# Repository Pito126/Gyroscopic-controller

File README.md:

# Gyroscopic Controller

Gyroskopický ovladač postavený na mikrokontroléru **ESP32**. Tento projekt umožňuje snadné ovládání zařízení (např. her, robotů nebo dronů) pomocí pohybu ruky nebo zařízení díky vestavěnému gyroskopu a akcelerometru.

## Funkce
- **Detekce pohybu**: Real-time čtení dat z gyroskopu pro detekci rotace a akcelerace.
- **Bezdrátové připojení**: Podpora Wi-Fi a Bluetooth přes ESP32 pro snadnou integraci s aplikacemi.
- **Snadná konfigurace**: Použití Arduino IDE nebo PlatformIO pro rychlý vývoj.
- **Open-source hardware**: Kompatibilní s běžnými senzory jako MPU6050 nebo LSM6DS3 (upravte podle vašeho setupu).

## Diagramy a schémata

### Schéma zapojení (PNG)
Zde je schéma zapojení ESP32 s gyroskopickým senzorem MPU6050:

### Schéma PCB zapojení (PNG)
Zde je schéma PCB zapojení ESP32 s gyroskopickým senzorem MPU6050:

## Požadavky
- **Hardware**:
  - ESP32 development board (např. ESP32-WROOM-32).
  - Gyroskopický senzor (např. MPU6050 připojený přes I2C).
  - Jumper wires a breadboard pro prototypování.
- **Software**:
  - Arduino IDE (verze 2.0+) s ESP32 board support.
  - Knihovny: `Wire` (pro I2C), `MPU6050` (pokud používáte tento senzor) – instalujte přes Library Manager.

## Instalace
1. Nainstalujte Arduino IDE z [oficiálního webu](https://www.arduino.cc/en/software).
2. Přidejte podporu pro ESP32: V IDE jděte do **File > Preferences**, přidejte URL `https://raw.githubusercontent.com/espressif/arduino-esp32/gh-pages/package_esp32_index.json` do Additional Board Manager URLs a nainstalujte "esp32" z Board Manager.
3. Stáhněte si tento repozitář: `git clone https://github.com/Pito126/Gyroscopic-controller.git`.
4. Otevřete soubory `.ino` v Arduino IDE.
5. Nahrajte kód na ESP32 přes USB.

## Použití
1. Připojte gyroskopický senzor k ESP32 (příklad pro MPU6050):
   - VCC → 3.3V
   - GND → GND
   - SCL → GPIO 22
   - SDA → GPIO 21
2. Nahrajte sketch (příklad v `src/main.ino` – upravte podle vašeho kódu).
3. Otevřete Serial Monitor (115200 baud) pro sledování dat pohybu.

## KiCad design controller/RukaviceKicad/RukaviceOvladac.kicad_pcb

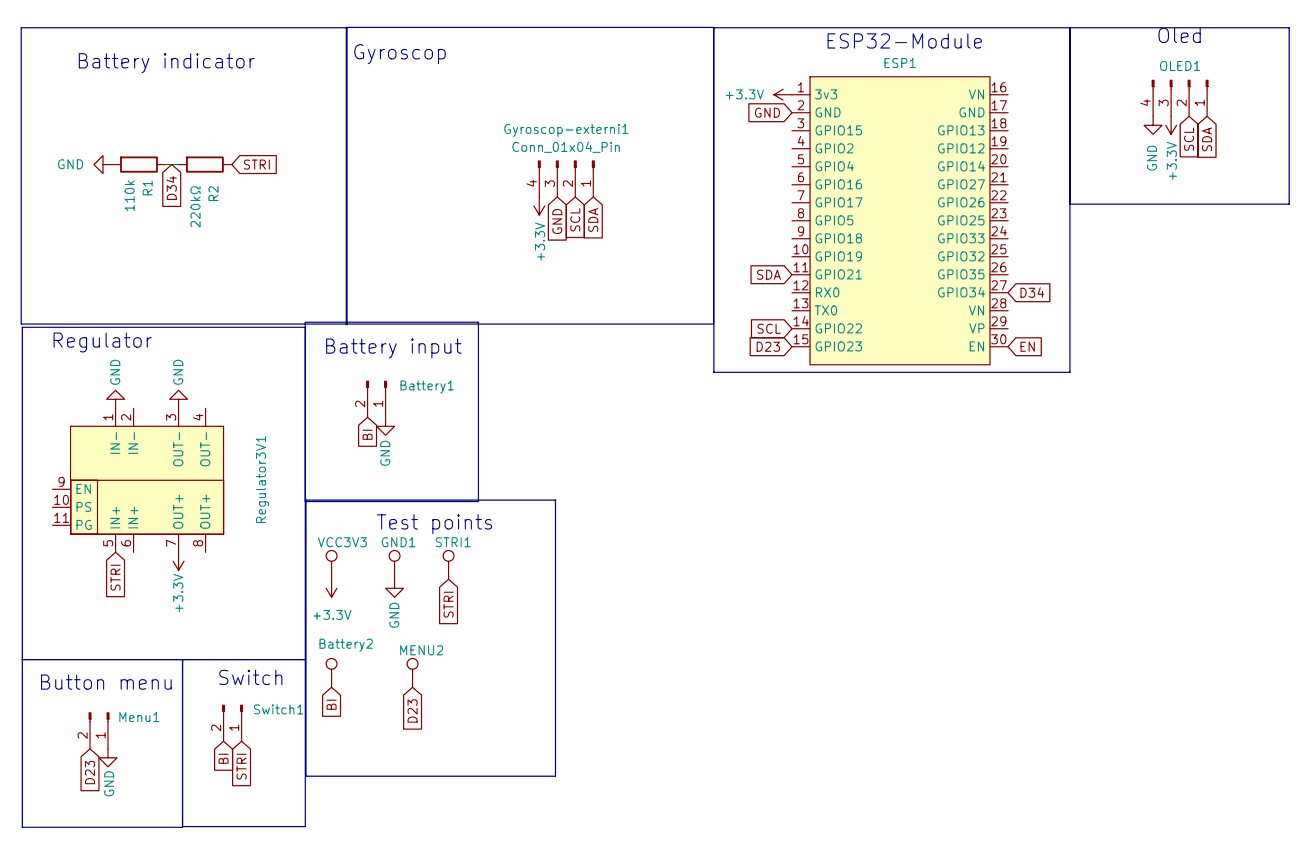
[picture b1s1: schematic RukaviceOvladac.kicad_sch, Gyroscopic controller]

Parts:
Battery1: Conn_01x02_Pin; JST_PH_B2B-PH-K_1x02_P2.00mm_Vertical
Battery2: TestPoint_Pad_1.0x1.0mm
ESP1: ESP32_30Pin_Module
GND1: TestPoint_Pad_1.0x1.0mm
Gyroscop-externi1: Conn_01x04_Pin; JST_PH_B4B-PH-K_1x04_P2.00mm_Vertical
MENU2: TestPoint_Pad_1.0x1.0mm
Menu1: Conn_01x02_Pin; JST_PH_B2B-PH-K_1x02_P2.00mm_Vertical
OLED1: Conn_01x04_Pin; JST_PH_B4B-PH-K_1x04_P2.00mm_Vertical
R1: 110k; R_Axial_DIN0207_L6.3mm_D2.5mm_P10.16mm_Horizontal
R2: 220kΩ; R_Axial_DIN0207_L6.3mm_D2.5mm_P10.16mm_Horizontal
Regulator3V1: Regulator3V3
STRI1: TestPoint_Pad_1.0x1.0mm
Switch1: Conn_01x02_Pin; JST_PH_B2B-PH-K_1x02_P2.00mm_Vertical
VCC3V3: TestPoint_Pad_1.0x1.0mm

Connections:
+3.3V: ESP1.1 (3v3), Gyroscop-externi1.4, OLED1.3, Regulator3V1.7 (OUT+), VCC3V3.1
BI: Battery1.2, Battery2.1, Switch1.2
D23: ESP1.15 (GPIO23), MENU2.1, Menu1.2
D34: ESP1.27 (GPIO34), R1.1, R2.2
EN: ESP1.30 (EN)
GND: Battery1.1, ESP1.2 (GND), GND1.1, Gyroscop-externi1.3, Menu1.1, OLED1.4, R1.2, Regulator3V1.1 (IN-), Regulator3V1.3 (OUT-)
SCL: ESP1.14 (GPIO22), Gyroscop-externi1.2, OLED1.2
SDA: ESP1.11 (GPIO21), Gyroscop-externi1.1, OLED1.1
STRI: R2.1, Regulator3V1.5 (IN+), STRI1.1, Switch1.1

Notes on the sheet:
Button menu
ESP32-Module
Gyroscop
Regulator
Oled
Battery indicator
Battery input
Switch
Test points

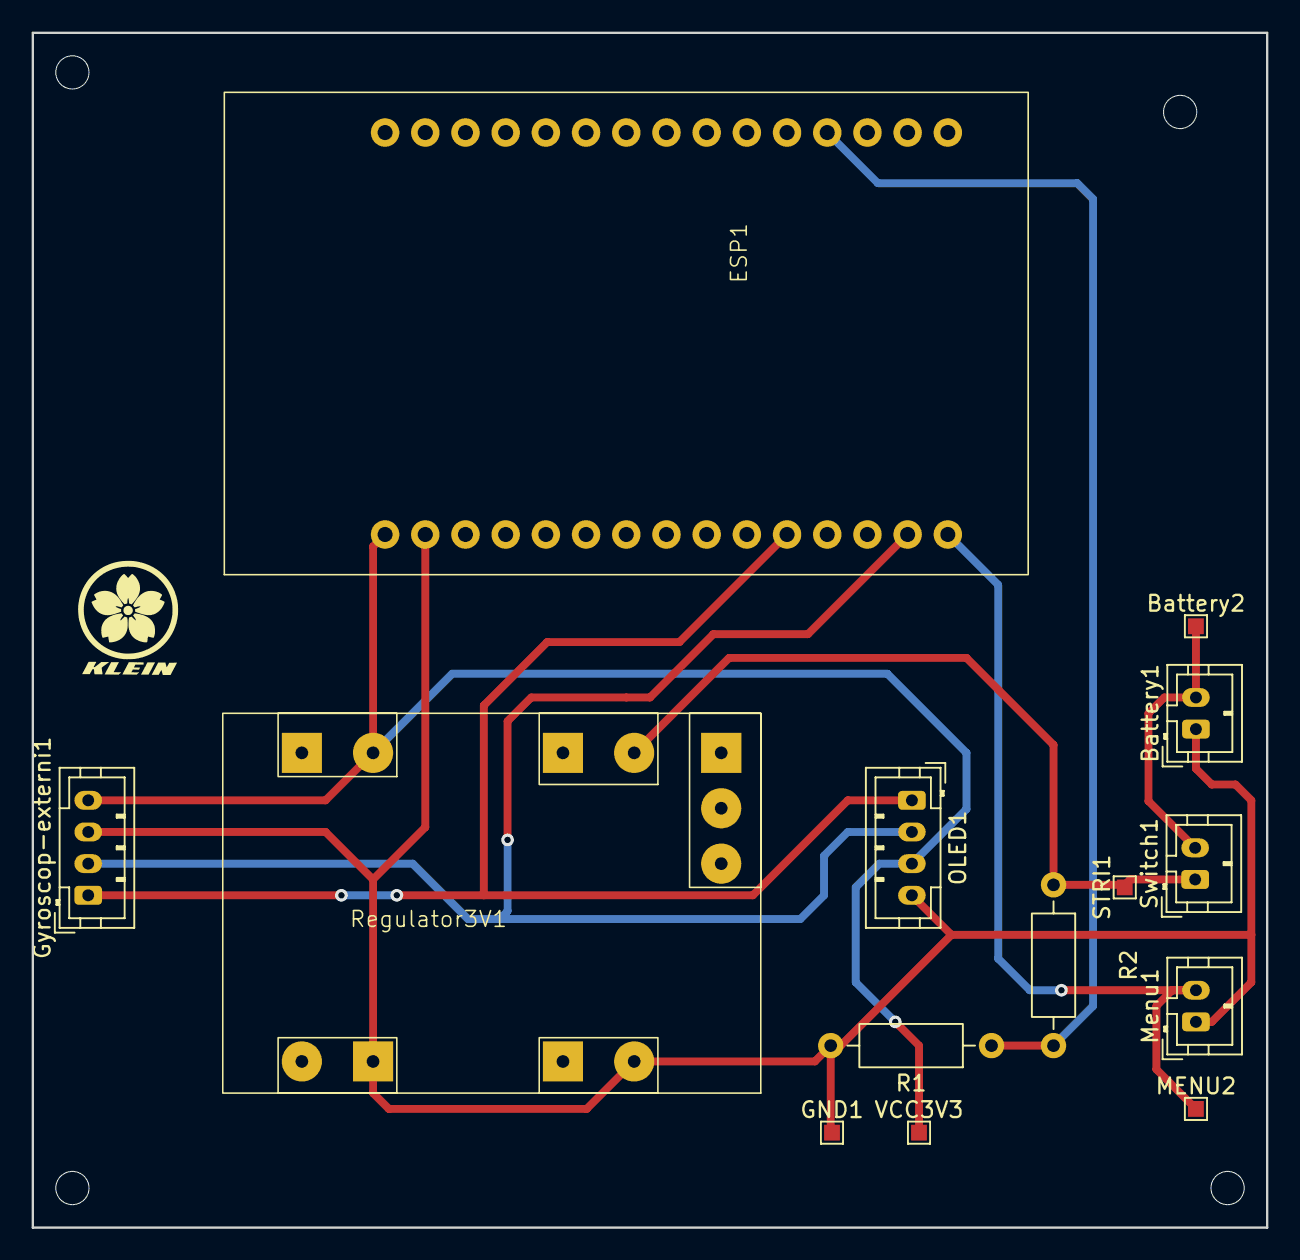
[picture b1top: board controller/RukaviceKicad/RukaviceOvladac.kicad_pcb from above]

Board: 2 copper layers, 78.0 x 75.5 mm, 14 parts (0 on the bottom side), 8 nets.

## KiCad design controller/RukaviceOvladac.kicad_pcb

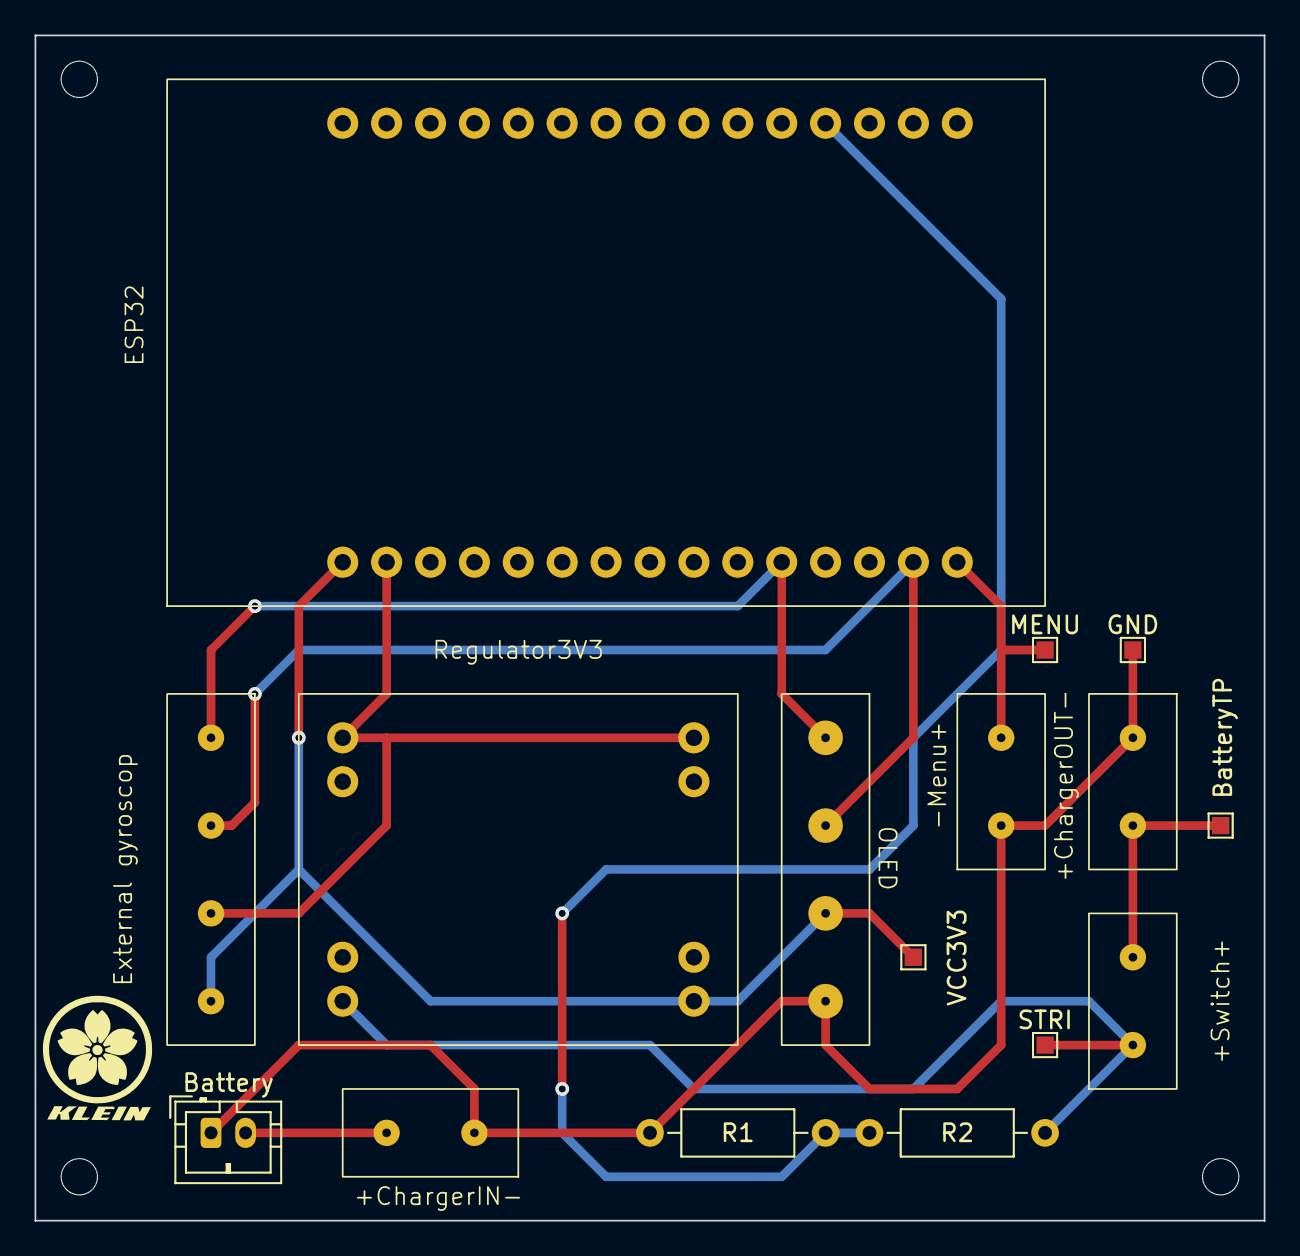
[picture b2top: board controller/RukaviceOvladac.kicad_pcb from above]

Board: 2 copper layers, 71.1 x 68.6 mm, 16 parts (0 on the bottom side), 9 nets.

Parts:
+ChargerIN-: Conn_01x02_Pin; Tlacitko
+ChargerOUT-: Conn_01x02_Pin; Tlacitko
+Switch+: Conn_01x02_Pin; Tlacitko
-Menu+: Conn_01x02_Pin; Tlacitko
Battery: Conn_01x02_Pin; JST_PH_B2B-PH-K_1x02_P2.00mm_Vertical
BatteryTP: TestPoint_Pad_1.0x1.0mm
ESP32: ESP32_30Pin_Module
External gyroscop: Conn_01x04_Pin; Gyroskop-externi
GND: TestPoint_Pad_1.0x1.0mm
MENU: TestPoint_Pad_1.0x1.0mm
OLED: Conn_01x04_Pin; OLED
R1: 110k; R_Axial_DIN0207_L6.3mm_D2.5mm_P10.16mm_Horizontal
R2: 220kΩ; R_Axial_DIN0207_L6.3mm_D2.5mm_P10.16mm_Horizontal
Regulator3V3: Regulator
STRI: TestPoint_Pad_1.0x1.0mm
VCC3V3: TestPoint_Pad_1.0x1.0mm

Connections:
CHI+: +ChargerIN-.2, Battery.2
CHO+: +ChargerOUT-.2, +Switch+.2, BatteryTP.1
D23: -Menu+.2, ESP32.15 (GPIO23), MENU.1
D34: ESP32.27 (GPIO34), R1.1, R2.2
GND: +ChargerIN-.1, +ChargerOUT-.1, -Menu+.1, Battery.1, ESP32.2 (GND), External gyroscop.3, GND.1, OLED.4, R1.2, Regulator3V3.1 (IN-), Regulator3V3.5 (OUT-)
SCL: ESP32.14 (GPIO22), External gyroscop.2, OLED.2
SDA: ESP32.11 (GPIO21), External gyroscop.1, OLED.1
STRI: +Switch+.1, R2.1, Regulator3V3.4 (IN+), STRI.1
VCC3V3: ESP32.1 (3v3), External gyroscop.4, OLED.3, Regulator3V3.8 (OUT+), VCC3V3.1

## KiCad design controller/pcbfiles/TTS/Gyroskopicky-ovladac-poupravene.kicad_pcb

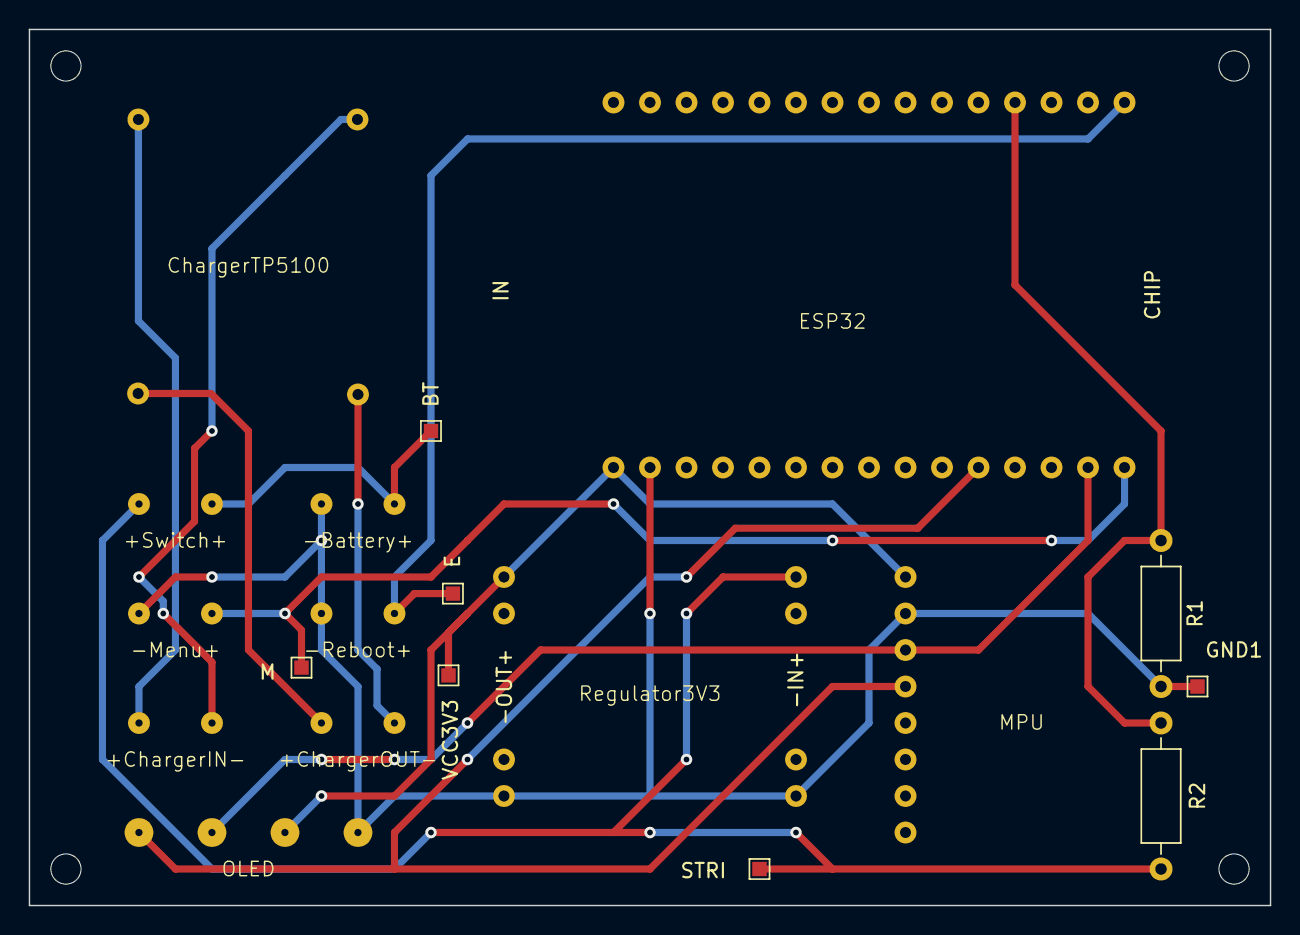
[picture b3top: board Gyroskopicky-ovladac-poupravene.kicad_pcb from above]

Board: 2 copper layers, 86.4 x 61.0 mm, 19 parts (0 on the bottom side), 13 nets.

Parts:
+ChargerIN-: Conn_01x02_Pin; Tlacitko
+ChargerOUT-: Conn_01x02_Pin; Tlacitko
+Switch+: Conn_01x02_Pin; Tlacitko
-Battery+: Conn_01x02_Pin; Tlacitko
-Menu+: Conn_01x02_Pin; Tlacitko
-Reboot+: Conn_01x02_Pin; Tlacitko
BT: TestPoint_Pad_1.0x1.0mm
ChargerTP5100: TP5100
E: TestPoint_Pad_1.0x1.0mm
ESP32: ESP32_30Pin_Module
GND1: TestPoint_Pad_1.0x1.0mm
M: TestPoint_Pad_1.0x1.0mm
MPU: Gyroskop
OLED: Conn_01x04_Pin; OLED
R1: 110k; R_Axial_DIN0207_L6.3mm_D2.5mm_P10.16mm_Horizontal
R2: 220kΩ; R_Axial_DIN0207_L6.3mm_D2.5mm_P10.16mm_Horizontal
Regulator3V3: Regulator
STRI: TestPoint_Pad_1.0x1.0mm
VCC3V3: TestPoint_Pad_1.0x1.0mm

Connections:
BTSI: +Switch+.2, -Battery+.2, BT.1
CHI+: +ChargerIN-.2, ChargerTP5100.2 (IN+)
CHI-: +ChargerIN-.1, ChargerTP5100.1 (IN-)
CHO+: +ChargerOUT-.1, ChargerTP5100.4 (OUT+)
CHO-: +ChargerOUT-.2, ChargerTP5100.3 (OUT-)
D23: -Menu+.2, ESP32.15 (GPIO23), M.1
D34: ESP32.27 (GPIO34), R1.1, R2.2
EN: -Reboot+.2, E.1, ESP32.30 (EN)
GND: -Battery+.1, -Menu+.1, -Reboot+.1, ESP32.2 (GND), GND1.1, MPU.2 (GND), OLED.4, R1.2, Regulator3V3.1 (IN-), Regulator3V3.5 (OUT-)
SCL: ESP32.14 (GPIO22), MPU.3 (SCL), OLED.2
SDA: ESP32.11 (GPIO21), MPU.4 (SDA), OLED.1
STRI: +Switch+.1, R2.1, Regulator3V3.4 (IN+), STRI.1
VCC3V3: ESP32.1 (3v3), MPU.1 (VCC), OLED.3, Regulator3V3.8 (OUT+), VCC3V3.1

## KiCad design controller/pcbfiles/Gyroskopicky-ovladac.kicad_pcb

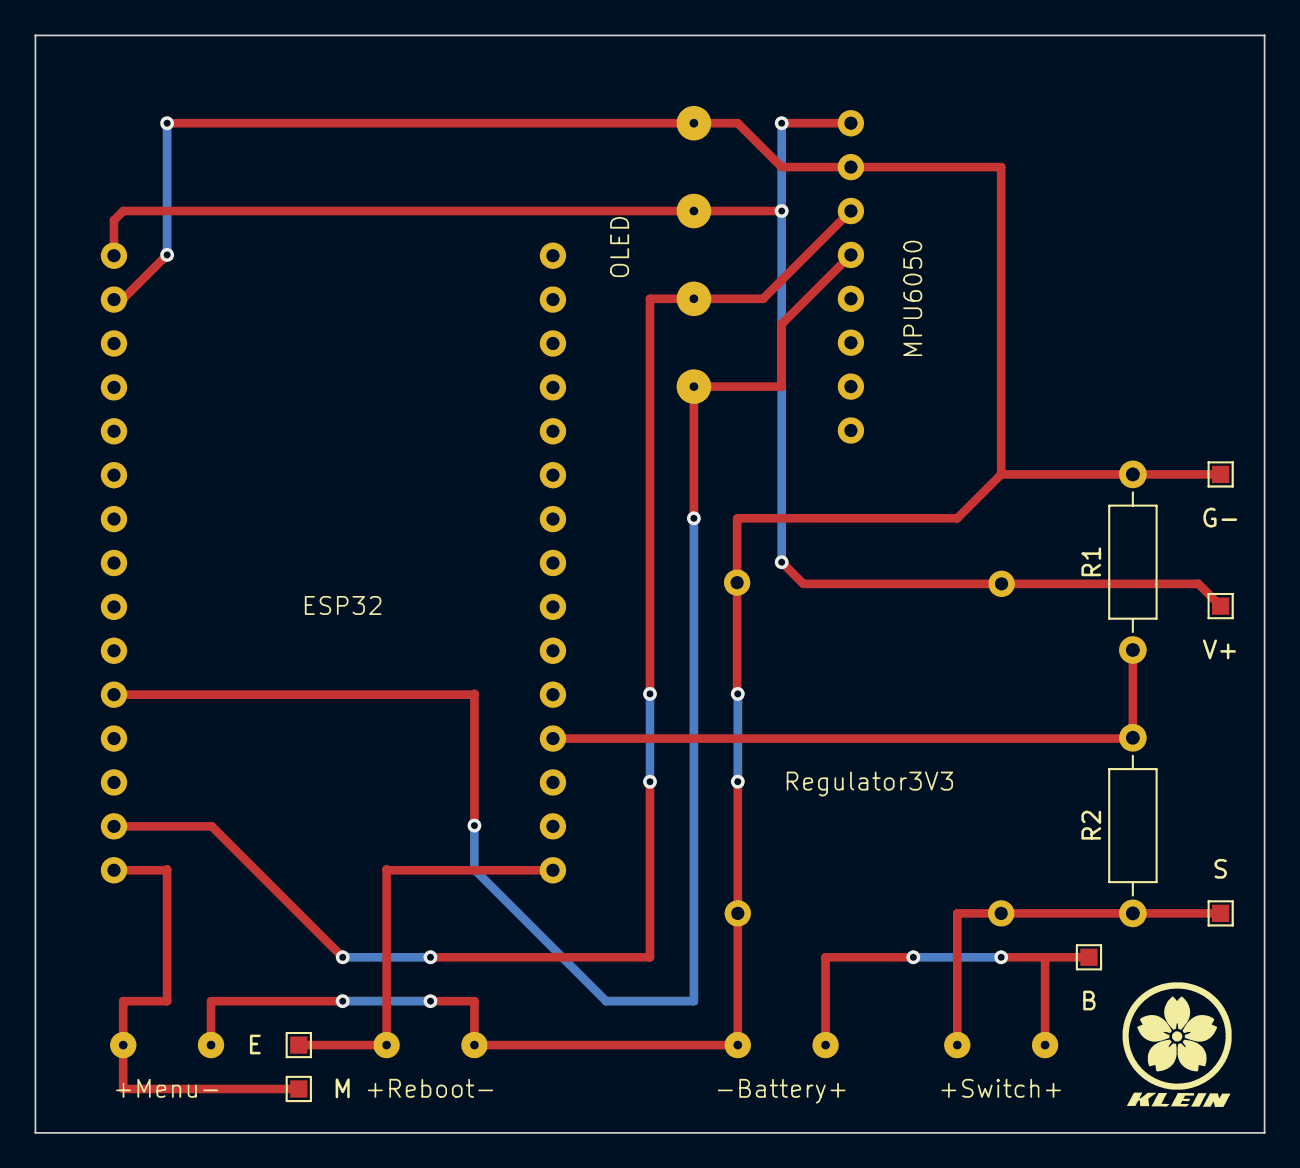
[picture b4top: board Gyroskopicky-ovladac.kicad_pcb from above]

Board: 2 copper layers, 71.1 x 63.5 mm, 17 parts (0 on the bottom side), 9 nets.

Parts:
+Menu-: Conn_01x02_Pin; Tlacitko
+Reboot-: Conn_01x02_Pin; Tlacitko
+Switch+: Conn_01x02_Pin; Tlacitko
-Battery+: Conn_01x02_Pin; Tlacitko
B: TestPoint_Pad_1.0x1.0mm
E: TestPoint_Pad_1.0x1.0mm
ESP32: ESP32_30Pin_Module
G-: TestPoint_Pad_1.0x1.0mm
M: TestPoint_Pad_1.0x1.0mm
MPU6050: Gyroskop
OLED: Conn_01x04_Pin; OLED
R1: 110k; R_Axial_DIN0207_L6.3mm_D2.5mm_P10.16mm_Horizontal
R2: 220kΩ; R_Axial_DIN0207_L6.3mm_D2.5mm_P10.16mm_Horizontal
Regulator3V3: Regulator
S: TestPoint_Pad_1.0x1.0mm
V+: TestPoint_Pad_1.0x1.0mm
kvetLogo: LOGO; logoKvet

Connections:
BTSI: +Switch+.2, -Battery+.2, B.1
D23: +Menu-.2, ESP32.15 (GPIO23), M.1
D34: ESP32.27 (GPIO34), R1.1, R2.2
EN: +Reboot-.2, E.1, ESP32.30 (EN)
GND: +Menu-.1, +Reboot-.1, -Battery+.1, ESP32.2 (GND), G-.1, MPU6050.2 (GND), OLED.4, R1.2, Regulator3V3.1 (IN-), Regulator3V3.3 (OUT-)
SCL: ESP32.14 (GPIO22), MPU6050.3 (SCL), OLED.2
SDA: ESP32.11 (GPIO21), MPU6050.4 (SDA), OLED.1
STRI: +Switch+.1, R2.1, Regulator3V3.2 (IN+), S.1
VCC3V3: ESP32.1 (3v3), MPU6050.1 (VCC), OLED.3, Regulator3V3.4 (OUT+), V+.1

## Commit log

2025-10-25 Rename Sender004-opravenyKruh.ino to sender/Sender004-opravenyKruh.ino
2025-10-25 Rename Funkcni_motordriver_reciever.ino to reciever/Funkcni_motordriver_reciever.ino
2025-10-29 Rename Gyroscopic-controller-scheme.pdf to schemes/Gyroscopic-controller-scheme.pdf
2025-10-29 Rename Gyroscopic controller - pcb.png to Gyroscopic-controller-pcb.png
2025-10-30 Create a
2025-10-30 Rename controller/Gyroscopic-controller-pcb.png to controller/schemes/Gyroscopic-controller-pcb.png
2025-10-30 Rename controller/Gyroscopic-controller-scheme.png to controller/schemes/Gyroscopic-controller-scheme.png
